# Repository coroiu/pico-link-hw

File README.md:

# Pico Link — custom hardware

Custom PCB and 3D-printed enclosure design for
[Pico Link](https://github.com/coroiu/pico-link), a USB-to-Bluetooth LDAC
audio dongle with a screen. This repo replaces the two stacked off-the-shelf
dev boards the project currently runs on with a single purpose-built board,
designed for JLCPCB fab + assembly.

See the design doc for the full rationale:
[`docs/plans/2026-11-13-custom-hardware-design.md`](docs/plans/2026-11-13-custom-hardware-design.md).

## Layout

- `hardware/` — KiCad project: schematic, PCB, footprints, BOM/JLCPCB part numbers.
- `enclosure/` — OpenSCAD source for the 3D-printed case.
- `docs/plans/` — design docs.
- `.planning/`, `.research/` — decision records and research findings, kept
  separate from the ephemeral issue tracker (see `AGENTS.md`).

Both `hardware/` and `enclosure/` are placeholders pending the next
implementation pass — see the design doc's "Deliverables" section.

## Status

No firmware lives in this repo — that's [coroiu/pico-link](https://github.com/coroiu/pico-link).
This repo only tracks the physical design: PCB, BOM, enclosure.

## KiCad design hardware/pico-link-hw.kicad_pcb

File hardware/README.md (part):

# Hardware

KiCad project goes here: schematic, PCB layout, footprints, and a BOM with
JLCPCB/LCSC part numbers.

## Project skeleton (pilink-7el.1)

`pico-link-hw.kicad_pro` / `pico-link-hw.kicad_sch` is the root KiCad 8
project. The root sheet holds one hierarchical sheet symbol per subsystem,
each pointing at its own (currently empty) child `.kicad_sch`:

- `power.kicad_sch` — power subsystem (pilink-7el.2)
- `rp2350b_memory.kicad_sch` — RP2350B + flash/PSRAM (pilink-7el.3)
- `esp32_bt.kicad_sch` — ESP32-WROOM-32UE BT coprocessor (pilink-7el.4, amended by pilink-wot)
- `display.kicad_sch` — ST7789V display (pilink-7el.5)
- `input.kicad_sch` — buttons + volume/menu encoder (pilink-7el.6, amended by pilink-cmn then pilink-3rm)
- `usb_c.kicad_sch` — USB-C connector (pilink-7el.7)

All six child sheets started out intentionally empty — no components, no
nets — so later beads can populate them independently. See "Deliverables" in
[`../docs/plans/2026-11-13-custom-hardware-design.md`](../docs/plans/2026-11-13-custom-hardware-design.md)
for subsystem scope, and `.planning/decisions/` for the component choices
already settled (MCU, radio coprocessor, display, memory, the 2026-11-14
d-pad-instead-of-joystick input decision, and the two 2026-11-15
rotary-encoder amendments that first replaced LEFT/RIGHT and then
UP/DOWN).

### Power subsystem (pilink-7el.2)

`power.kicad_sch` now has the 3.3V rail: USB-C 5V in (via a `+5V`/`PWR_FLAG`
pair, pending the USB-C sheet, pilink-7el.7) through U1, a SOT-223 LDO, to
a single `+3V3` rail, with a 10uF input bulk cap (C1), a 22uF output bulk
cap (C2), and a 100nF local decoupler (C3) at the point of load.
Component choice and decoupling values are cross-checked against Raspberry
Pi's own official RP2350B minimal reference design and RP2350 Hardware
Design Guide (RP-008280-DS) — see the citations in the sheet's own text
notes. RP2350B's internal 3.3V→1.1V switched-mode core regulator (inductor,
feedback caps) and its per-pin VDD3V3/IOVDD decoupling belong on the
RP2350B + Memory sheet (pilink-7el.3), not here, matching the same split
used in Raspberry Pi's reference design.

U1 was originally an AMS1117-3.3 (bipolar NPN-pass, JLCPCB Basic part
C6186/LCSC C6186). `pilink-ddq` found its near-fixed ~1.2-1.3V dropout
offset left too little margin against USB VBUS's worst-case floor once a
tripped VBUS PTC fuse (F401, see the USB-C sheet below) was counted in, and
swapped it for AP2114H-3.3TRG1 (BCD Semiconductor/Diodes Incorporated,
LCSC `C150716`, 10,090 units in stock) — a genuinely CMOS-process LDO
whose real datasheet guarantees 450mV (typ)/750mV (max) dropout at 1A and
>=1.0A (min) guaranteed output current, pin-compatible with the AMS1117 it
replaces (same SOT-223-3_TabPin2 footprint, 1=GND/2=VOUT/3=VIN) so no
layout rework was needed. C1/C2 (10uF/22uF ceramic) already exceed this
part's own 4.7uF-ceramic stability requirement, so neither cap needed to
change. See `power.kicad_sch`'s own U1 note for the full resolved margin
math.

**U1 thermal check and bring-up flags (pilink-mxx).** Neither is a
regression from the AMS1117 (same SOT-223 exposure); both were left open
by `pilink-ddq` and are recorded here so they are not assumed fine:

- *Thermal (layout time).* AP2114H-3.3TRG1's datasheet gives roughly
  128°C/W junction-to-ambient for the bare SOT-223, a 150°C maximum
  junction temperature and a ~160°C thermal shutdown. Dissipation is
  (VIN - 3.3V) x I. Sustained worst case, 5.25V VIN at 0.65A: 1.27W, a
  162°C rise on the bare package -- over the 150°C limit even from 0°C.
  Realistic case, 5.0V at ~0.2A average (RP2350B, display, and an ESP32
  average of ~80mA -- an estimate, not an Espressif datasheet figure):
  ~0.34W, a ~44°C rise, comfortable. The 0.65A figure is the ESP32
  TX-burst *peak* (ms-scale), not a sustained load, so the real exposure
  sits between those two. To hold the 150°C limit under the sustained
  worst case at 40°C ambient the layout would need junction-to-ambient
  below ~87°C/W (~99°C/W at 25°C), about a third below the bare package.
  The PCB design adds a +3V3 heat-spreader pour around U1's VOUT tab on
  both layers (`zones.py`) stitched with a via grid (once PR #72 merges:
  36 vias, ~270mm^2 filled), but no datasheet-backed number for the
  resulting junction-to-ambient exists, so this stays a **bench
  measurement**: record case temperature of U1 on the first board under
  the worst sustained load available before trusting the margin.
- *Bring-up (bench).* AP2114H-3.3's datasheet limits short-circuit current
  to ~50mA (foldback) and says input must be applied before a
  current-source load is connected. Verify on the first board that +3V3
  starts cleanly into the full rail and its bulk capacitance (C2 22uF
  plus the per-pin decouplers), with no latch-up in a slow or stalled
  ramp; scope the +3V3 rise at power-up and after an F401 PTC trip/reset.

Unlike the rest of this skeleton, this sheet **was** validated with the real
tools: `kicad-cli sch erc --severity-all --exit-code-violations` reports 0
violations on both `power.kicad_sch` and the root `pico-link-hw.kicad_sch`,
and the exported PDF was visually checked for a sane, non-overlapping
layout. The other four child sheets remain unverified skeletons.

### RP2350B + Memory subsystem (pilink-7el.3)

`rp2350b_memory.kicad_sch` now has the RP2350B (QFN-80), 12MHz crystal
(Abracon ABM8-272-T3), BOOTSEL + reset buttons, 16MB QSPI NOR flash
(Winbond W25Q128JVS) and 8MB QSPI PSRAM (AP Memory APS6404L-3SQR-ZR), plus
the RP2350B-specific decoupling flagged as out-of-scope at the end of
`power.kicad_sch`'s own notes: the internal 3.3V→1.1V switched-mode core
regulator's inductor/caps (L101, C103/C104/C105, R104) and the ~12
individual 100nF VDD3V3/IOVDD decouplers. Every value and part choice is
cross-checked against primary sources (Raspberry Pi's own RP2350B minimal
reference design, the RP2350 hardware design guide, Pimoroni's published
Pico Plus 2 schematic, and distributor listings for the PSRAM's actual
package) — see the sheet's own text notes for citations, including two
corrections to this bead's own framing (the external LDO's bulk caps don't
belong on this sheet; the PSRAM's `-ZR` suffix is USON-8L, not SOIC-8).

U101's symbol and QFN-80 footprint come from Raspberry Pi's own historical
RP2350B minimal-reference-design KiCad archive (RP-006442-DD-2) — not the
third-party HDR/RP2350_KiCad repo flagged as "untested" in this bead's
acceptance criteria. (U101 is this sheet's RP2350B; `power.kicad_sch`'s
AMS1117 regulator is U1 — an earlier review round found the two had been
confused via a cross-sheet reference collision, fixed by renumbering this
whole sheet into the 100-199 block: U101-U103, C101-C121, R101-R105,
SW101-SW102, L101, Y101, with power.kicad_sch keeping 1-99 and
esp32_bt.kicad_sch taking 200-299; a netlist export confirms no reference
collides anywhere in the project hierarchy.) The footprint is copied into
`hardware/footprints/RP2350_80QFN.pretty/` (registered in `fp-lib-table`);
the RP2350 and PSRAM symbols are also registered as proper project
libraries in `hardware/symbols/` + `sym-lib-table` so KiCad's GUI resolves
them instead of only trusting the schematic's embedded cache.

Every RP2350B GPIO not consumed by this sheet is brought out as a global
label matching its pin name, so the other still-empty child sheets can pick
it up later without hierarchical sheet pins. GPIO47 is withheld from this
pool (committed to the PSRAM's chip-select here), and so are 8 more GPIOs
(GPIO0/1/4/5/6/7/20/21) whose `GPIOn` label was replaced, in place, by the
matching `ESP32_*` name — see the "ESP32 BT coprocessor subsystem" section
below for that assignment (`pilink-kt4`).

`kicad-cli sch erc --severity-all` on this sheet **alone** (KiCad
10.0.8) reports 2 errors (`power_pin_not_driven` for `+3V3`/`GND`,
expected and documented in the sheet's own notes — this sheet doesn't
generate `+3V3`/`GND`, `power.kicad_sch` does, so a standalone
single-sheet ERC run can't see that driver) and 54 warnings: 51
`isolated_pin_label` ("Label connected to only one pin") for GPIO labels
whose other end lives on a sibling sheet this standalone, single-sheet
check can't see — this now includes the 8 `ESP32_*` labels too, for the
same reason the pre-existing +3V3/GND check can't see `power.kicad_sch`
in isolation, not a new defect — plus 1 `footprint_link_issues` and 2
`lib_symbol_issues` notices, pre-existing and unrelated to this change
(this project's custom footprint/symbol libraries aren't registered in
the global table this standalone invocation uses).

`kicad-cli sch erc --severity-all --exit-code-violations` on the **root**
`pico-link-hw.kicad_sch` (which flattens the whole hierarchy and does see
every sibling sheet, the check that reflects real connectivity) reports
**0 errors, 26 warnings**, all `isolated_pin_label` on `GPIOn` labels this
project genuinely hasn't assigned to anything yet (GPIO2/3/8-19/35-39/
42-46) plus the pre-existing `SWD`/`SWCLK` labels — none of the 8
`ESP32_*` labels remain in this list, confirming `pilink-kt4`'s fix; see
the ESP32 section below for the before/after numbers and root cause. The
stale "Symbol has been modified in library" notice from an earlier round
no longer appears; it was fixed by re-syncing the embedded flash symbol to
the stock library part.

Schematic connectivity (the netlist export and both ERC runs above) is
verified clean. The visual layout went through two review rounds of
reported cosmetic text/label overlaps — a text note overlapping nearby
component labels, a power-flag symbol sitting on top of a note, and a
couple of reference labels landing on top of net labels; none of these
affect the netlist or ERC results. Every overlap reported across both
rounds has now been moved into clear canvas space, and the sheet was
re-exported to SVG and visually re-checked after the fixes; none remain
as of this revision. This is still an agent-driven check against a
rendered export, not a human sign-off in the KiCad GUI, so treat it as a
good-faith check rather than a final layout approval.

### ESP32 BT coprocessor subsystem (pilink-7el.4, amended by pilink-wot)

`esp32_bt.kicad_sch` now has U201 (ESP32-WROOM-32UE-N4, KiCad's built-in
`RF_Module:ESP32-WROOM-32UE` symbol/footprint, pinout cross-checked pin-by-
pin against Espressif's own datasheet Table 3 -- originally against the
32D/32U datasheet in pilink-7el.4, re-confirmed identical against the
32E/32UE datasheet by research bead pilink-8zj), EN strapping (R201 10k +
C203 1uF RC delay, per Espressif's Hardware Design Guidelines Schematic
Checklist), GPIO0/BOOT0 strapping (R202 10k pull-up only, no cap, per the
same checklist), and 3V3 decoupling (C201 10uF + C202 100nF). GPIO2 is
left floating (no pull), relying on its internal pull-down for Joint
Download Boot, matching stock ESP32 dev boards. (References here use the
200-299 block under this project's per-sheet reference-numbering scheme
--  power.kicad_sch keeps 1-99 (already merged as U1/C1/C2/C3/#PWR01-09),
rp2350b_memory.kicad_sch gets 100-199, and esp32_bt.kicad_sch gets
200-299 (U201, C201-C203, R201-R202, #PWR201-209) -- so no two sibling
sheets' components can ever merge into the same netlist part. KiCad
merges same-reference parts across sibling sheets into one netlist part,
so without non-overlapping ranges per sheet, reusing references would
silently corrupt the project netlist; see the PR review discussion on
pilink-7el.4 (and the matching fix on pilink-7el.3) for details.)

RP2350 interface: exposed via **global labels** (not hierarchical --
`esp32_bt.kicad_sch` and `rp2350b_memory.kicad_sch` are sibling child
sheets, so a hierarchical label would need root-sheet pin wiring that
doesn't exist yet; a global label joins same-named nets project-wide
without it): `ESP32_EN`, `ESP32_BOOT0`, `ESP32_HCI_TXD/RXD/RTS/CTS`,
`ESP32_FLASH_TXD0/RXD0`. See the sheet's own text notes for the full
rationale and citations.

**RP2350-side GPIO assignment (`pilink-kt4`):** these 8 global labels
previously had no RP2350-side counterpart at all --
`rp2350b_memory.kicad_sch` only exposed its pins as generic `GPIOn`
labels, so every `ESP32_*` net was single-ended (one pad, `U201` only)
in the exported netlist, and ERC never caught it because a standalone
global label is legal. Fixed by replacing 8 of that sheet's `GPIOn`
global labels, in place, with these `ESP32_*` names, picked from the
[RP2350 datasheet](https://datasheets.raspberrypi.com/rp2350/rp2350-datasheet.pdf)
section 9.4, "GPIO Bank 0 Functions" (RP2350B has exactly 2 UART
peripherals, UART0/UART1, confirmed from that section, not assumed;
cited by section rather than table number since table numbering has
shifted across datasheet revisions):

| Net | RP2350 GPIO (pin) | Function |
| --- | --- | --- |
| `ESP32_HCI_RXD` | GPIO4 (pin 1) | UART1 TX (F2) |
| `ESP32_HCI_TXD` | GPIO5 (pin 2) | UART1 RX (F2) |
| `ESP32_HCI_RTS` | GPIO6 (pin 3) | UART1 CTS (F2) |
| `ESP32_HCI_CTS` | GPIO7 (pin 4) | UART1 RTS (F2) |
| `ESP32_FLASH_RXD0` | GPIO0 (pin 77) | UART0 TX (F2) |
| `ESP32_FLASH_TXD0` | GPIO1 (pin 78) | UART0 RX (F2) |
| `ESP32_EN` | GPIO20 (pin 20) | plain GPIO (bit-banged) |
| `ESP32_BOOT0` | GPIO21 (pin 21) | plain GPIO (bit-banged) |

UART1 (GPIO4-7) carries the HCI link as a full 4-wire group with
hardware flow control, matching the "4-wire HCI UART, not optional"
requirement in
[`.planning/decisions/2026-11-13-esp32-bt-coprocessor-not-rm2.md`](../.planning/decisions/2026-11-13-esp32-bt-coprocessor-not-rm2.md);
RTS/CTS cross modem-style (ESP32's RTS output lands on RP2350's CTS
input, and vice versa). UART0 (GPIO0/1) carries only the esptool
bridge-flashing link, which needs no flow control. GPIO20/21 (freed
back into the generic pool by `pilink-3rm`'s d-pad-to-encoder swap) are
plain bit-banged outputs for EN/BOOT0 strapping -- no peripheral
function needed. All 8 GPIOs were confirmed free by grepping every
populated sheet's actual `global_label`/`label` usage (not just their
absence as a generic `GPIOn` label on this one sheet) before picking
them.

Flash variant: ESP32-WROOM-32UE-**N4** (JLCPCB/LCSC `C701344`). Sufficient
for an HCI-controller-only firmware image (no Wi-Fi/Bluedroid/display
code); live LCSC stock checked 2026-11-14 (research bead pilink-8zj) at
~3,321 units, comfortably above any realistic build quantity. (Before the
`pilink-wot` swap below, this was ESP32-WROOM-32U-**N4**, JLCPCB/LCSC
`C328062`, with stock in the low thousands of units.)

**Risk flag resolved (`pilink-wot`):** Espressif's datasheet (v2.8,
2026-09-16) marked ESP32-WROOM-32U "NOT RECOMMENDED FOR NEW DESIGNS
(NRND)" -- not surfaced in the original ADR, and flagged as a follow-up
risk by bead `pilink-8zj`. Stock was still healthy and the part was still
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
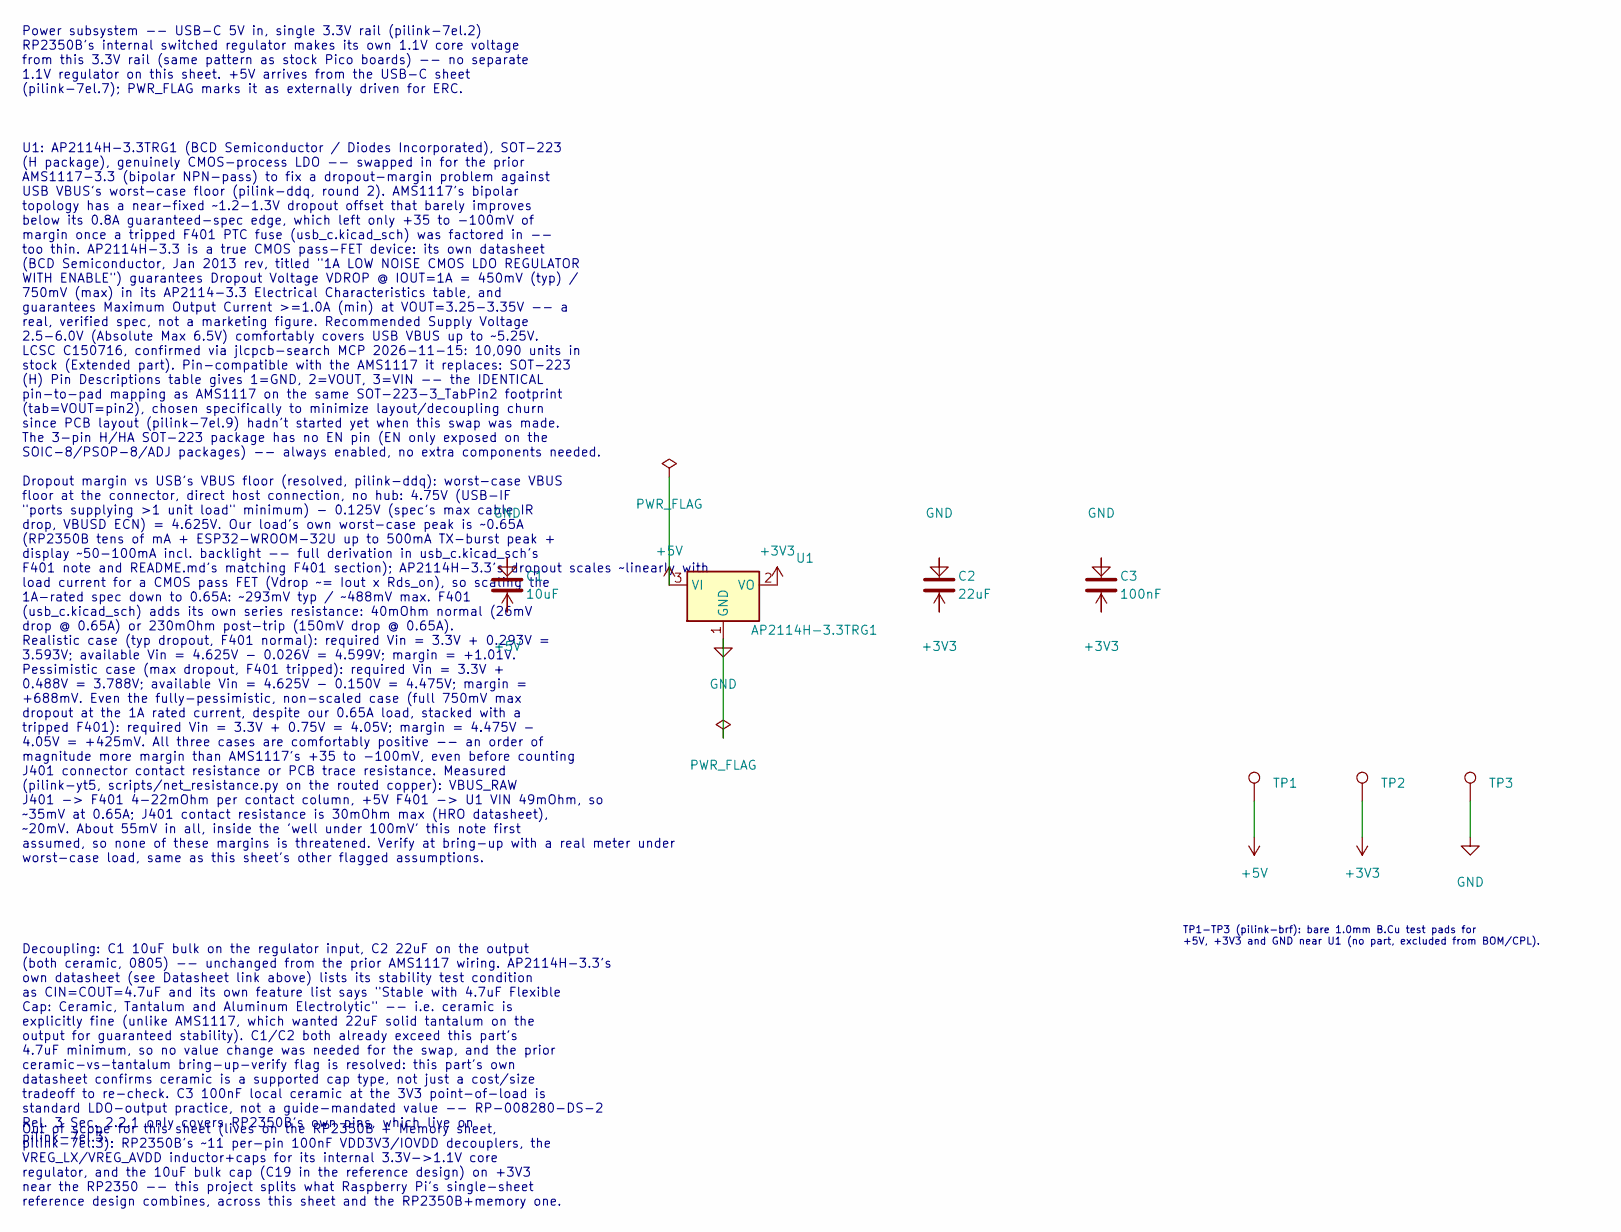
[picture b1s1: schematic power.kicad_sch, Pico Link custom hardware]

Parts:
C1: 10uF; C_0805_2012Metric
C2: 22uF; C_0805_2012Metric
C3: 100nF; C_0402_1005Metric
TP1: +5V; TestPoint_Pad_D1.0mm
TP2: +3V3; TestPoint_Pad_D1.0mm
TP3: GND; TestPoint_Pad_D1.0mm
U1: AP2114H-3.3TRG1; SOT-223-3_TabPin2

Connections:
+3V3: C2.2, C3.2, TP2.1, U1.2 (VO); also elsewhere on the board
+5V: C1.2, TP1.1, U1.3 (VI); also elsewhere on the board
GND: C1.1, C2.1, C3.1, TP3.1, U1.1 (GND); also elsewhere on the board

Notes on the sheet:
Power subsystem -- USB-C 5V in, single 3.3V rail (pilink-7el.2) RP2350B's internal switched regulator makes its own 1.1V core voltage from this 3.3V rail (same pattern as stock Pico boards) -- no separate 1.1V regulator on this sheet. +5V arrives from the USB-C sheet (pilink-7el.7); PWR_FLAG marks 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
U1: AP2114H-3.3TRG1 (BCD Semiconductor / Diodes Incorporated), SOT-223 (H package), genuinely CMOS-process LDO -- swapped in for the prior AMS1117-3.3 (bipolar NPN-pass) to fix a dropout-margin problem against USB VBUS's worst-case floor (pilink-ddq, round 2). AMS1117's bipolar topology has a near-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
Decoupling: C1 10uF bulk on the regulator input, C2 22uF on the output (both ceramic, 0805) -- unchanged from the prior AMS1117 wiring. AP2114H-3.3's own datasheet (see Datasheet link above) lists its stability test condition as CIN=COUT=4.7uF and its own feature list says "Stable with 4.7uF Flexib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
Out of scope for this sheet (lives on the RP2350B + Memory sheet, pilink-7el.3): RP2350B's ~11 per-pin 100nF VDD3V3/IOVDD decouplers, the VREG_LX/VREG_AVDD inductor+caps for its internal 3.3V->1.1V core regulator, and the 10uF bulk cap (C19 in the reference design) on +3V3 near the RP2350 -- this p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
TP1-TP3 (pilink-brf): bare 1.0mm B.Cu test pads for +5V, +3V3 and GND near U1 (no part, excluded from BOM/CPL).

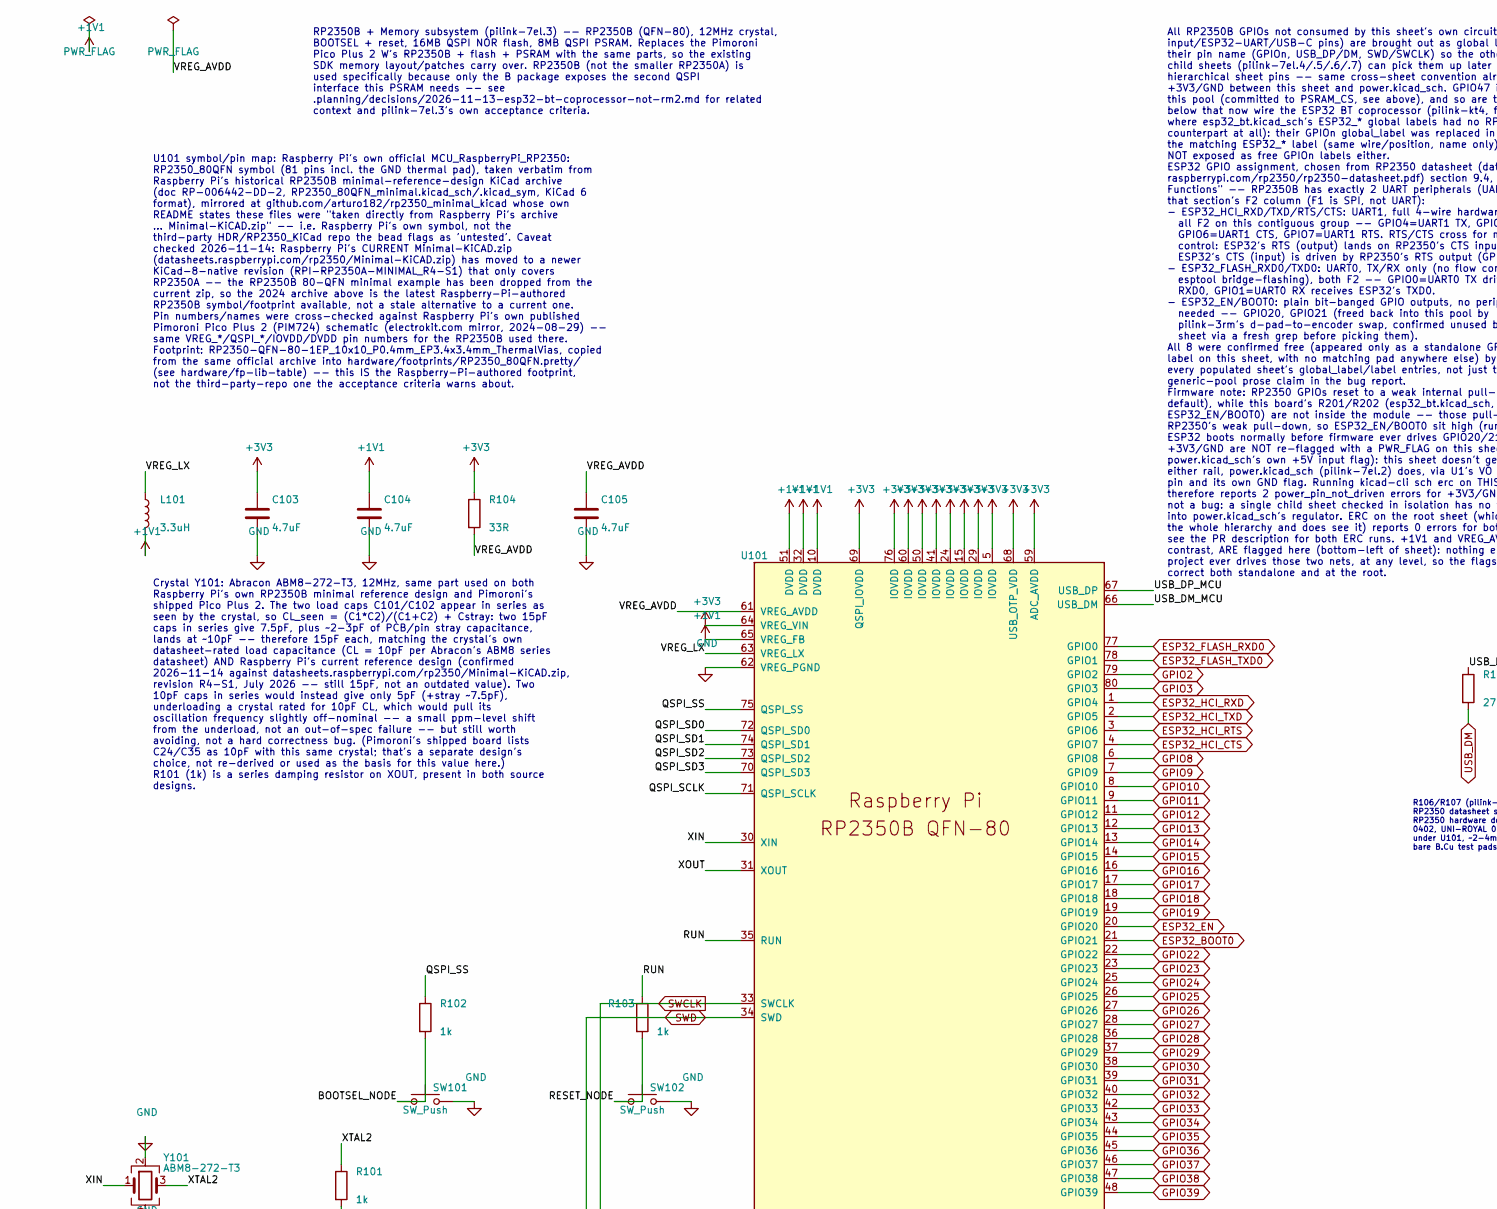
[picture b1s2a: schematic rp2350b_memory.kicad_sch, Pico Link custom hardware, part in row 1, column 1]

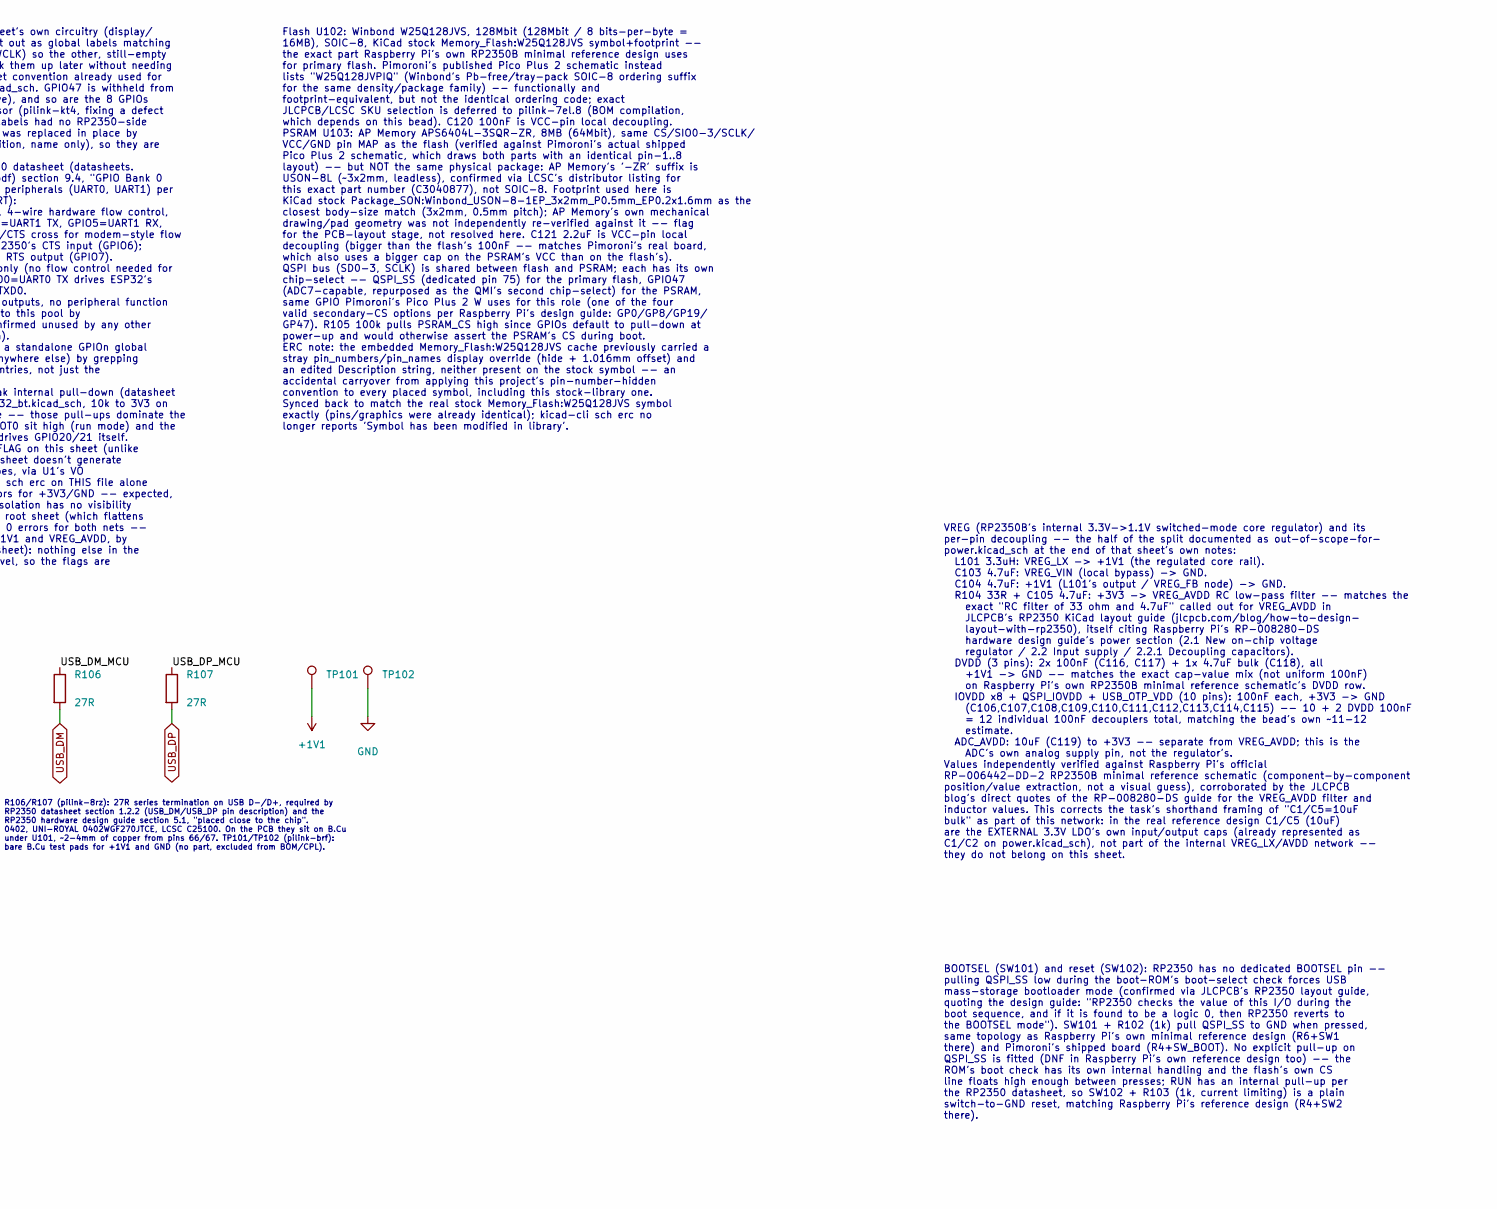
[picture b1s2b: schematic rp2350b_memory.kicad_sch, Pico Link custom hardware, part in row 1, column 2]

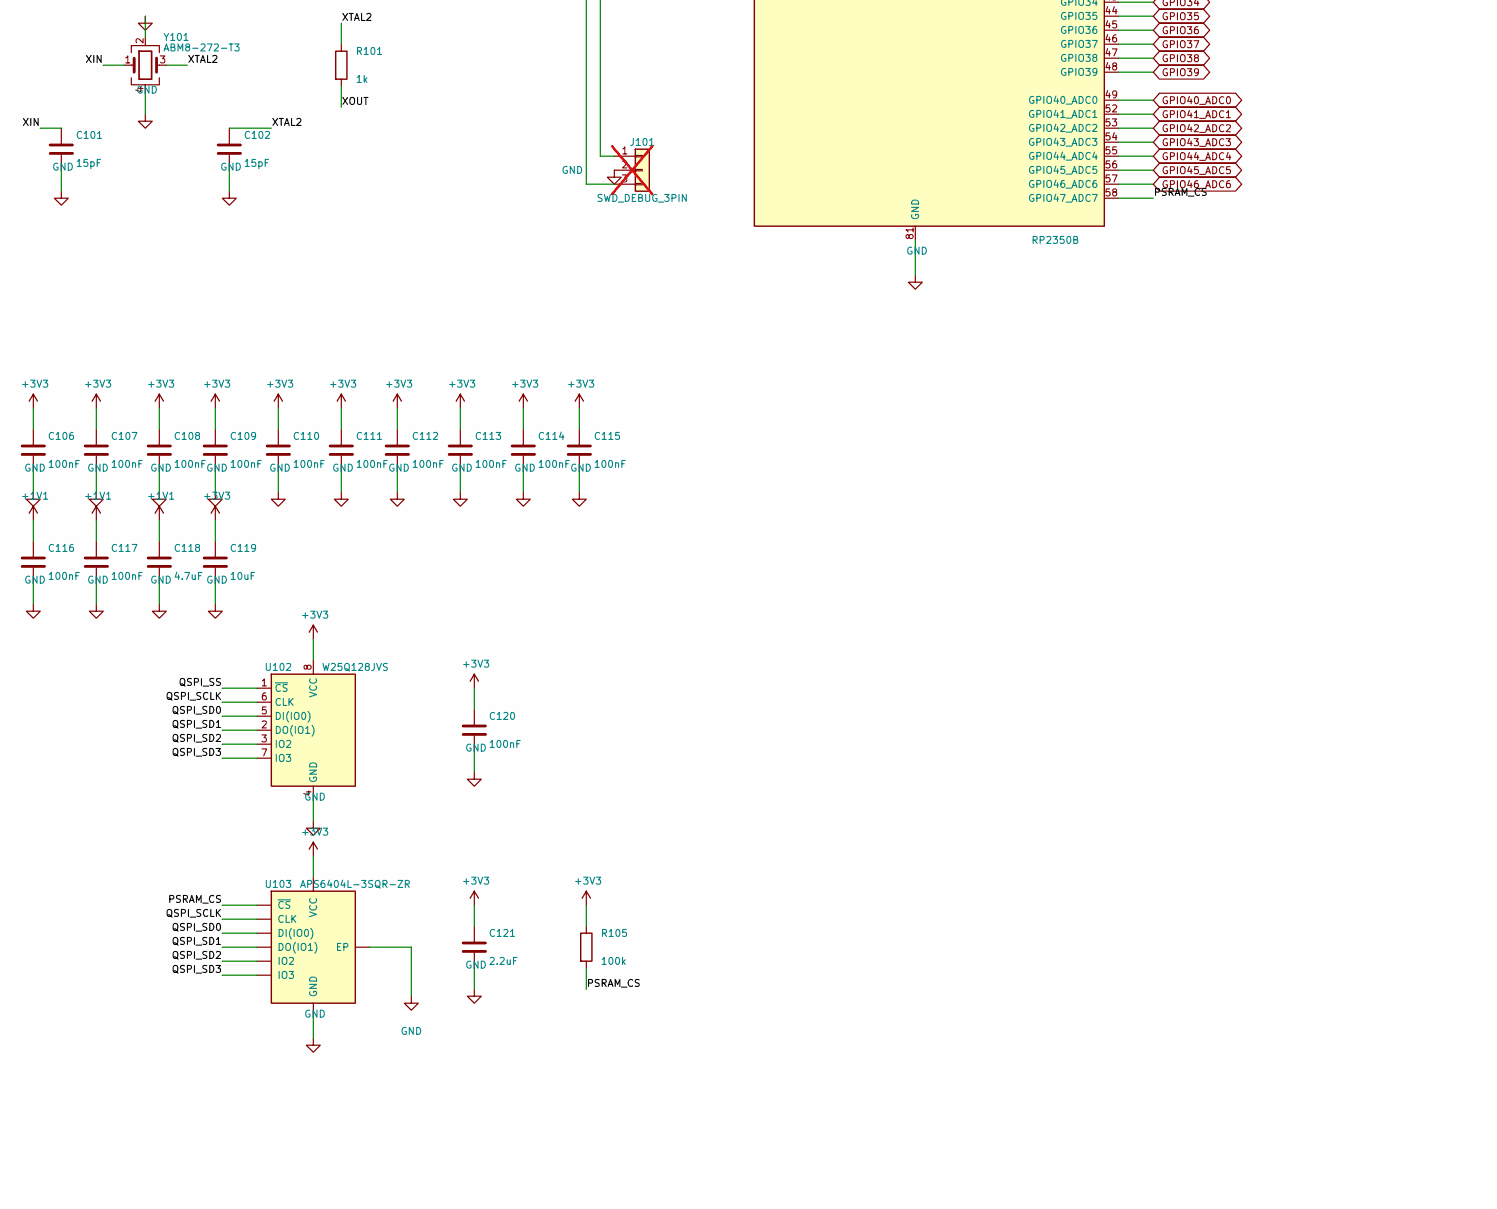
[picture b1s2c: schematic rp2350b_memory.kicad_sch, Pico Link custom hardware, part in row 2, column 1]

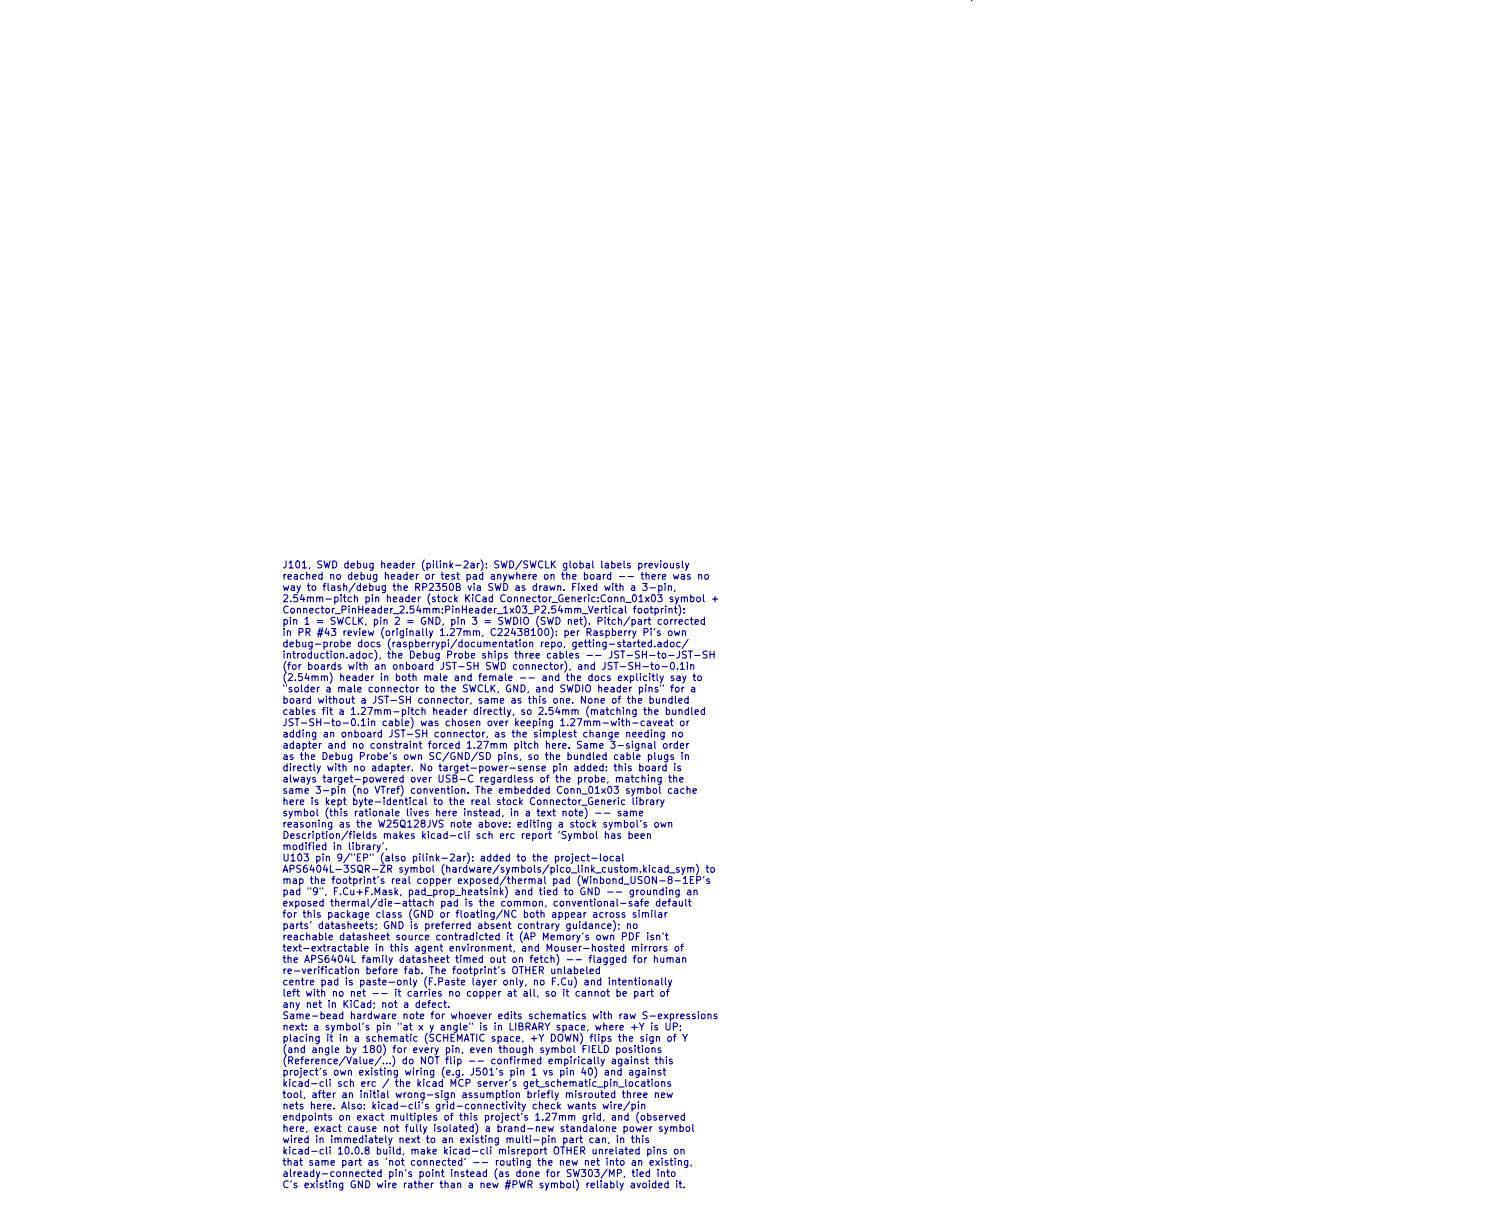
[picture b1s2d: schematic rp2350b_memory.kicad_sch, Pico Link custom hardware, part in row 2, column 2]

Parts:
C101, C102: 15pF; C_0402_1005Metric
C103, C104, C105, C118: 4.7uF; C_0402_1005Metric
C106, C107, C108, C109, C110, C111, C112, C113, C114, C115, C116, C117, C120: 100nF; C_0402_1005Metric
C119: 10uF; C_0805_2012Metric
C121: 2.2uF; C_0603_1608Metric
J101: SWD_DEBUG_3PIN; PinHeader_1x03_P2.54mm_Vertical; not fitted
L101: 3.3uH; L_DMBJ_CXP0420
R101, R102, R103: 1k; R_0402_1005Metric
R104: 33R; R_0402_1005Metric
R105: 100k; R_0402_1005Metric
R106, R107: 27R; R_0402_1005Metric
SW101, SW102: SW_Push; SW_Push_1P1T-MP_NO_Horizontal_Alps_SKRTLAE010
TP101: +1V1; TestPoint_Pad_D1.0mm
TP102: GND; TestPoint_Pad_D1.0mm
U101: RP2350B; RP2350-QFN-80-1EP_10x10_P0.4mm_EP3.4x3.4mm_ThermalVias
U102: W25Q128JVS; SOIC-8_5.23x5.23mm_P1.27mm
U103: APS6404L-3SQR-ZR; Winbond_USON-8-1EP_3x2mm_P0.5mm_EP0.2x1.6mm
Y101: ABM8-272-T3; Crystal_SMD_3225-4Pin_3.2x2.5mm

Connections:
+1V1: C104.1, C116.1, C117.1, C118.1, L101.2, TP101.1, U101.10 (DVDD), U101.32 (DVDD), U101.51 (DVDD), U101.65 (VREG_FB)
+3V3: C103.1, C106.1, C107.1, C108.1, C109.1, C110.1, C111.1, C112.1, C113.1, C114.1, C115.1, C119.1, C120.1, C121.1, R104.1, R105.1, U101.5 (IOVDD), U101.15 (IOVDD), U101.24 (IOVDD), U101.29 (IOVDD), U101.41 (IOVDD), U101.50 (IOVDD), U101.59 (ADC_AVDD), U101.60 (IOVDD), U101.64 (VREG_VIN), U101.68 (USB_OTP_VDD), U101.69 (QSPI_IOVDD), U101.76 (IOVDD), U102.8 (VCC), U103.8 (VCC); also elsewhere on the board
/RP2350B + Memory/BOOTSEL_NODE: R102.2, SW101.1
/RP2350B + Memory/PSRAM_CS: R105.2, U101.58 (GPIO47_ADC7), U103.1 (~CS)
/RP2350B + Memory/QSPI_SCLK: U101.71 (QSPI_SCLK), U102.6 (CLK), U103.6 (CLK)
/RP2350B + Memory/QSPI_SD0: U101.72 (QSPI_SD0), U102.5 (DI(IO0)), U103.5 (DI(IO0))
/RP2350B + Memory/QSPI_SD1: U101.74 (QSPI_SD1), U102.2 (DO(IO1)), U103.2 (DO(IO1))
/RP2350B + Memory/QSPI_SD2: U101.73 (QSPI_SD2), U102.3 (IO2), U103.3 (IO2)
/RP2350B + Memory/QSPI_SD3: U101.70 (QSPI_SD3), U102.7 (IO3), U103.7 (IO3)
/RP2350B + Memory/QSPI_SS: R102.1, U101.75 (QSPI_SS), U102.1 (~CS)
/RP2350B + Memory/RESET_NODE: R103.2, SW102.1
/RP2350B + Memory/RUN: R103.1, U101.35 (RUN)
/RP2350B + Memory/USB_DM_MCU: R106.1, U101.66 (USB_DM)
/RP2350B + Memory/USB_DP_MCU: R107.1, U101.67 (USB_DP)
/RP2350B + Memory/VREG_AVDD: C105.1, R104.2, U101.61 (VREG_AVDD)
/RP2350B + Memory/VREG_LX: L101.1, U101.63 (VREG_LX)
/RP2350B + Memory/XIN: C101.1, U101.30 (XIN), Y101.1
/RP2350B + Memory/XOUT: R101.2, U101.31 (XOUT)
/RP2350B + Memory/XTAL2: C102.1, R101.1, Y101.3
ESP32_BOOT0: U101.21 (GPIO21); also elsewhere on the board
ESP32_EN: U101.20 (GPIO20); also elsewhere on the board
ESP32_FLASH_RXD0: U101.77 (GPIO0); also elsewhere on the board
ESP32_FLASH_TXD0: U101.78 (GPIO1); also elsewhere on the board
ESP32_HCI_CTS: U101.4 (GPIO7); also elsewhere on the board
ESP32_HCI_RTS: U101.3 (GPIO6); also elsewhere on the board
ESP32_HCI_RXD: U101.1 (GPIO4); also elsewhere on the board
ESP32_HCI_TXD: U101.2 (GPIO5); also elsewhere on the board
GND: C101.2, C102.2, C103.2, C104.2, C105.2, C106.2, C107.2, C108.2, C109.2, C110.2, C111.2, C112.2, C113.2, C114.2, C115.2, C116.2, C117.2, C118.2, C119.2, C120.2, C121.2, J101.2, SW101.2, SW102.2, TP102.1, U101.62 (VREG_PGND), U101.81 (GND), U102.4 (GND), U103.4 (GND), U103.9 (EP), Y101.2, Y101.4; also elsewhere on the board
GPIO2: U101.79 (GPIO2)
GPIO3: U101.80 (GPIO3)
GPIO8: U101.6 (GPIO8)
GPIO9: U101.7 (GPIO9)
GPIO10: U101.8 (GPIO10)
GPIO11: U101.9 (GPIO11)
GPIO12: U101.11 (GPIO12)
GPIO13: U101.12 (GPIO13)
GPIO14: U101.13 (GPIO14)
GPIO15: U101.14 (GPIO15)
GPIO16: U101.16 (GPIO16)
GPIO17: U101.17 (GPIO17)
GPIO18: U101.18 (GPIO18)
GPIO19: U101.19 (GPIO19)
GPIO22: U101.22 (GPIO22); also elsewhere on the board
GPIO23: U101.23 (GPIO23); also elsewhere on the board
GPIO24: U101.25 (GPIO24); also elsewhere on the board
GPIO25: U101.26 (GPIO25); also elsewhere on the board
GPIO26: U101.27 (GPIO26); also elsewhere on the board
GPIO27: U101.28 (GPIO27); also elsewhere on the board
GPIO28: U101.36 (GPIO28); also elsewhere on the board
GPIO29: U101.37 (GPIO29); also elsewhere on the board
GPIO30: U101.38 (GPIO30); also elsewhere on the board
GPIO31: U101.39 (GPIO31); also elsewhere on the board
GPIO32: U101.40 (GPIO32); also elsewhere on the board
GPIO33: U101.42 (GPIO33); also elsewhere on the board
GPIO34: U101.43 (GPIO34); also elsewhere on the board
GPIO35: U101.44 (GPIO35)
GPIO36: U101.45 (GPIO36)
GPIO37: U101.46 (GPIO37)
GPIO38: U101.47 (GPIO38)
GPIO39: U101.48 (GPIO39)
GPIO40_ADC0: U101.49 (GPIO40_ADC0); also elsewhere on the board
GPIO41_ADC1: U101.52 (GPIO41_ADC1); also elsewhere on the board
GPIO42_ADC2: U101.53 (GPIO42_ADC2)
GPIO43_ADC3: U101.54 (GPIO43_ADC3)
GPIO44_ADC4: U101.55 (GPIO44_ADC4)
GPIO45_ADC5: U101.56 (GPIO45_ADC5)
GPIO46_ADC6: U101.57 (GPIO46_ADC6)
SWCLK: J101.1, U101.33 (SWCLK)
SWD: J101.3, U101.34 (SWD)
USB_DM: R106.2; also elsewhere on the board
USB_DP: R107.2; also elsewhere on the board

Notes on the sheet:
RP2350B + Memory subsystem (pilink-7el.3) -- RP2350B (QFN-80), 12MHz crystal, BOOTSEL + reset, 16MB QSPI NOR flash, 8MB QSPI PSRAM. Replaces the Pimoroni Pico Plus 2 W's RP2350B + flash + PSRAM with the same parts, so the existing SDK memory layout/patches carry over. RP2350B (not the smaller RP235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
U101 symbol/pin map: Raspberry Pi's own official MCU_RaspberryPi_RP2350: RP2350_80QFN symbol (81 pins incl. the GND thermal pad), taken verbatim from Raspberry Pi's historical RP2350B minimal-reference-design KiCad archive (doc RP-006442-DD-2, RP2350_80QFN_minimal.kicad_sch/.kicad_sym, KiCad 6 form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
Crystal Y101: Abracon ABM8-272-T3, 12MHz, same part used on both Raspberry Pi's own RP2350B minimal reference design and Pimoroni's shipped Pico Plus 2. The two load caps C101/C102 appear in series as seen by the crystal, so CL_seen = (C1*C2)/(C1+C2) + Cstray: two 15pF caps in series give 7.5pF, pl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
VREG (RP2350B's internal 3.3V->1.1V switched-mode core regulator) and its per-pin decoupling -- the half of the split documented as out-of-scope-for- power.kicad_sch at the end of that sheet's own notes: L101 3.3uH: VREG_LX -> +1V1 (the regulated core rail). C103 4.7uF: VREG_VIN (local bypass) -> G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
BOOTSEL (SW101) and reset (SW102): RP2350 has no dedicated BOOTSEL pin -- pulling QSPI_SS low during the boot-ROM's boot-select check forces USB mass-storage bootloader mode (confirmed via JLCPCB's RP2350 layout guide, quoting the design guide: "RP2350 checks the value of this I/O during the boot s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
Flash U102: Winbond W25Q128JVS, 128Mbit (128Mbit / 8 bits-per-byte = 16MB), SOIC-8, KiCad stock Memory_Flash:W25Q128JVS symbol+footprint -- the exact part Raspberry Pi's own RP2350B minimal reference design uses for primary flash. Pimoroni's published Pico Plus 2 schematic instead lists "W25Q128JVP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
J101, SWD debug header (pilink-2ar): SWD/SWCLK global labels previously reached no debug header or test pad anywhere on the board -- there was no way to flash/debug the RP2350B via SWD as drawn. Fixed with a 3-pin, 2.54mm-pitch pin header (stock KiCad Connector_Generic:Conn_01x03 symbol + Connector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
All RP2350B GPIOs not consumed by this sheet's own circuitry (display/ input/ESP32-UART/USB-C pins) are brought out as global labels matching their pin name (GPIOn, USB_DP/DM, SWD/SWCLK) so the other, still-empty child sheets (pilink-7el.4/.5/.6/.7) can pick them up later without needing hierarchic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
R106/R107 (pilink-8rz): 27R series termination on USB D-/D+, required by RP2350 datasheet section 1.2.2 (USB_DM/USB_DP pin description) and the RP2350 hardware design guide section 5.1, "placed close to the chip". 0402, UNI-ROYAL 0402WGF270JTCE, LCSC C25100. On the PCB they sit on B.Cu under U101, 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

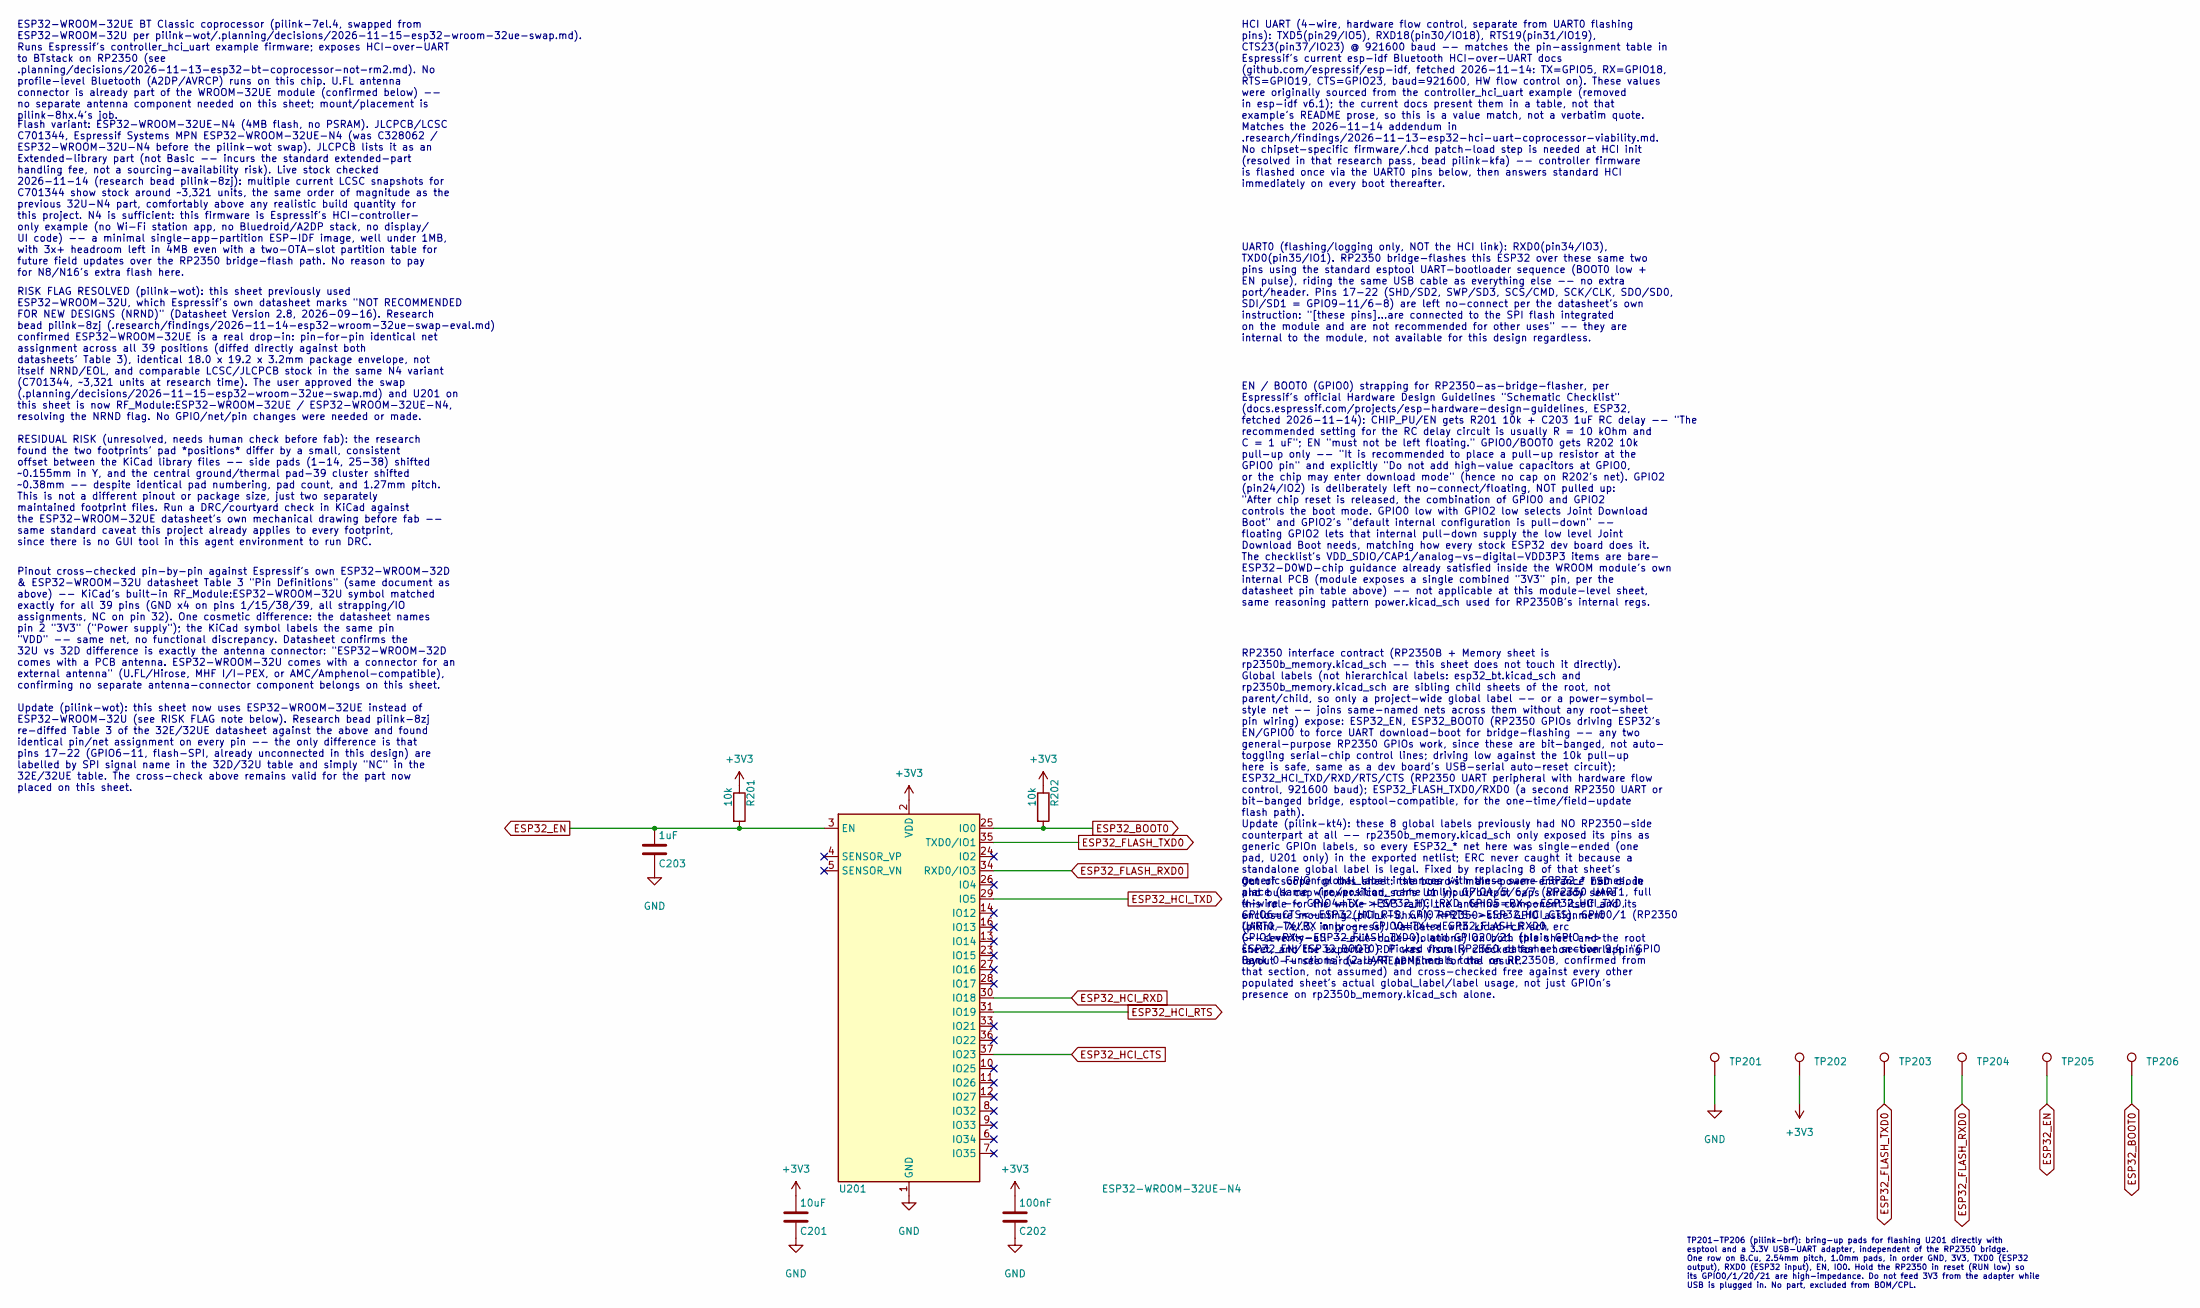
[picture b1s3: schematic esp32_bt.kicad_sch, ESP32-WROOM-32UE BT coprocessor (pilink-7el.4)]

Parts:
C201: 10uF; C_0805_2012Metric
C202: 100nF; C_0402_1005Metric
C203: 1uF; C_0603_1608Metric
R201, R202: 10k; R_0603_1608Metric
TP201: GND; TestPoint_Pad_D1.0mm
TP202: +3V3; TestPoint_Pad_D1.0mm
TP203: ESP32_FLASH_TXD0; TestPoint_Pad_D1.0mm
TP204: ESP32_FLASH_RXD0; TestPoint_Pad_D1.0mm
TP205: ESP32_EN; TestPoint_Pad_D1.0mm
TP206: ESP32_BOOT0; TestPoint_Pad_D1.0mm
U201: ESP32-WROOM-32UE-N4; ESP32-WROOM-32UE

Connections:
+3V3: C201.1, C202.1, R201.1, R202.1, TP202.1, U201.2 (VDD); also elsewhere on the board
ESP32_BOOT0: R202.2, TP206.1, U201.25 (IO0); also elsewhere on the board
ESP32_EN: C203.1, R201.2, TP205.1, U201.3 (EN); also elsewhere on the board
ESP32_FLASH_RXD0: TP204.1, U201.34 (RXD0/IO3); also elsewhere on the board
ESP32_FLASH_TXD0: TP203.1, U201.35 (TXD0/IO1); also elsewhere on the board
ESP32_HCI_CTS: U201.37 (IO23); also elsewhere on the board
ESP32_HCI_RTS: U201.31 (IO19); also elsewhere on the board
ESP32_HCI_RXD: U201.30 (IO18); also elsewhere on the board
ESP32_HCI_TXD: U201.29 (IO5); also elsewhere on the board
GND: C201.2, C202.2, C203.2, TP201.1, U201.1 (GND), U201.15 (GND), U201.38 (GND), U201.39 (GND); also elsewhere on the board

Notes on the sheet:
ESP32-WROOM-32UE BT Classic coprocessor (pilink-7el.4, swapped from ESP32-WROOM-32U per pilink-wot/.planning/decisions/2026-11-15-esp32-wroom-32ue-swap.md). Runs Espressif's controller_hci_uart example firmware; exposes HCI-over-UART to BTstack on RP2350 (see .planning/decisions/2026-11-13-esp32-bt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
Flash variant: ESP32-WROOM-32UE-N4 (4MB flash, no PSRAM). JLCPCB/LCSC C701344, Espressif Systems MPN ESP32-WROOM-32UE-N4 (was C328062 / ESP32-WROOM-32U-N4 before the pilink-wot swap). JLCPCB lists it as an Extended-library part (not Basic -- incurs the standard extended-part handling fee, not a sou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
RISK FLAG RESOLVED (pilink-wot): this sheet previously used ESP32-WROOM-32U, which Espressif's own datasheet marks "NOT RECOMMENDED FOR NEW DESIGNS (NRND)" (Datasheet Version 2.8, 2026-09-16). Research bead pilink-8zj (.research/findings/2026-11-14-esp32-wroom-32ue-swap-eval.md) confirmed ESP32-WRO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
Pinout cross-checked pin-by-pin against Espressif's own ESP32-WROOM-32D & ESP32-WROOM-32U datasheet Table 3 "Pin Definitions" (same document as above) -- KiCad's built-in RF_Module:ESP32-WROOM-32U symbol matched exactly for all 39 pins (GND x4 on pins 1/15/38/39, all strapping/IO assignments, NC on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
HCI UART (4-wire, hardware flow control, separate from UART0 flashing pins): TXD5(pin29/IO5), RXD18(pin30/IO18), RTS19(pin31/IO19), CTS23(pin37/IO23) @ 921600 baud -- matches the pin-assignment table in Espressif's current esp-idf Bluetooth HCI-over-UART docs (github.com/espressif/esp-idf, fetched 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
UART0 (flashing/logging only, NOT the HCI link): RXD0(pin34/IO3), TXD0(pin35/IO1). RP2350 bridge-flashes this ESP32 over these same two pins using the standard esptool UART-bootloader sequence (BOOT0 low + EN pulse), riding the same USB cable as everything else -- no extra port/header. Pins 17-22 (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
EN / BOOT0 (GPIO0) strapping for RP2350-as-bridge-flasher, per Espressif's official Hardware Design Guidelines "Schematic Checklist" (docs.espressif.com/projects/esp-hardware-design-guidelines, ESP32, fetched 2026-11-14): CHIP_PU/EN gets R201 10k + C203 1uF RC delay -- "The recommended setting for 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
RP2350 interface contract (RP2350B + Memory sheet is rp2350b_memory.kicad_sch -- this sheet does not touch it directly). Global labels (not hierarchical labels: esp32_bt.kicad_sch and rp2350b_memory.kicad_sch are sibling child sheets of the root, not parent/child, so only a project-wide global labe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
Out of scope for this sheet: the board's main-power-entrance ESD diode and bulk cap (power.kicad_sch's U1 input/output caps already serve this role for the whole +3V3 rail); the antenna component itself and its enclosure mounting (pilink-8hx.4); RP2350-side GPIO assignment (pilink-7el.3, in progres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
TP201-TP206 (pilink-brf): bring-up pads for flashing U201 directly with esptool and a 3.3V USB-UART adapter, independent of the RP2350 bridge. One row on B.Cu, 2.54mm pitch, 1.0mm pads, in order GND, 3V3, TXD0 (ESP32 output), RXD0 (ESP32 input), EN, IO0. Hold the RP2350 in reset (RUN low) so its GP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
